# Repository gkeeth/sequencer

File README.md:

# 8-step CV sequencer

Simple 8-step, 0-5V CV sequencer for synthesizers.

* Each step has an adjustable CV (0-5V)
* Clock is internally generated, but can also be provided externally
* Internal clock has adjustable frequency and duty cycle
* CV and clock outputs

Powered from a 9V battery.

This is a KiCad v7 project.

## License
Hardware design files are licensed under a [Creative Commons Attribution-ShareAlike 4.0
International License][cc-by-sa].

[![CC BY-SA 4.0][cc-by-sa-image]][cc-by-sa]

Code is licensed under the MIT license.

[![License: MIT][mit-shield]][mit-link]

[cc-by-sa]: http://creativecommons.org/licenses/by-sa/4.0/
[cc-by-sa-image]: https://licensebuttons.net/l/by-sa/4.0/88x31.png
[cc-by-sa-shield]: https://img.shields.io/badge/License-CC%20BY--SA%204.0-lightgrey.svg
[mit-link]: https://opensource.org/licenses/MIT
[mit-shield]: https://img.shields.io/badge/License-MIT-yellow.svg

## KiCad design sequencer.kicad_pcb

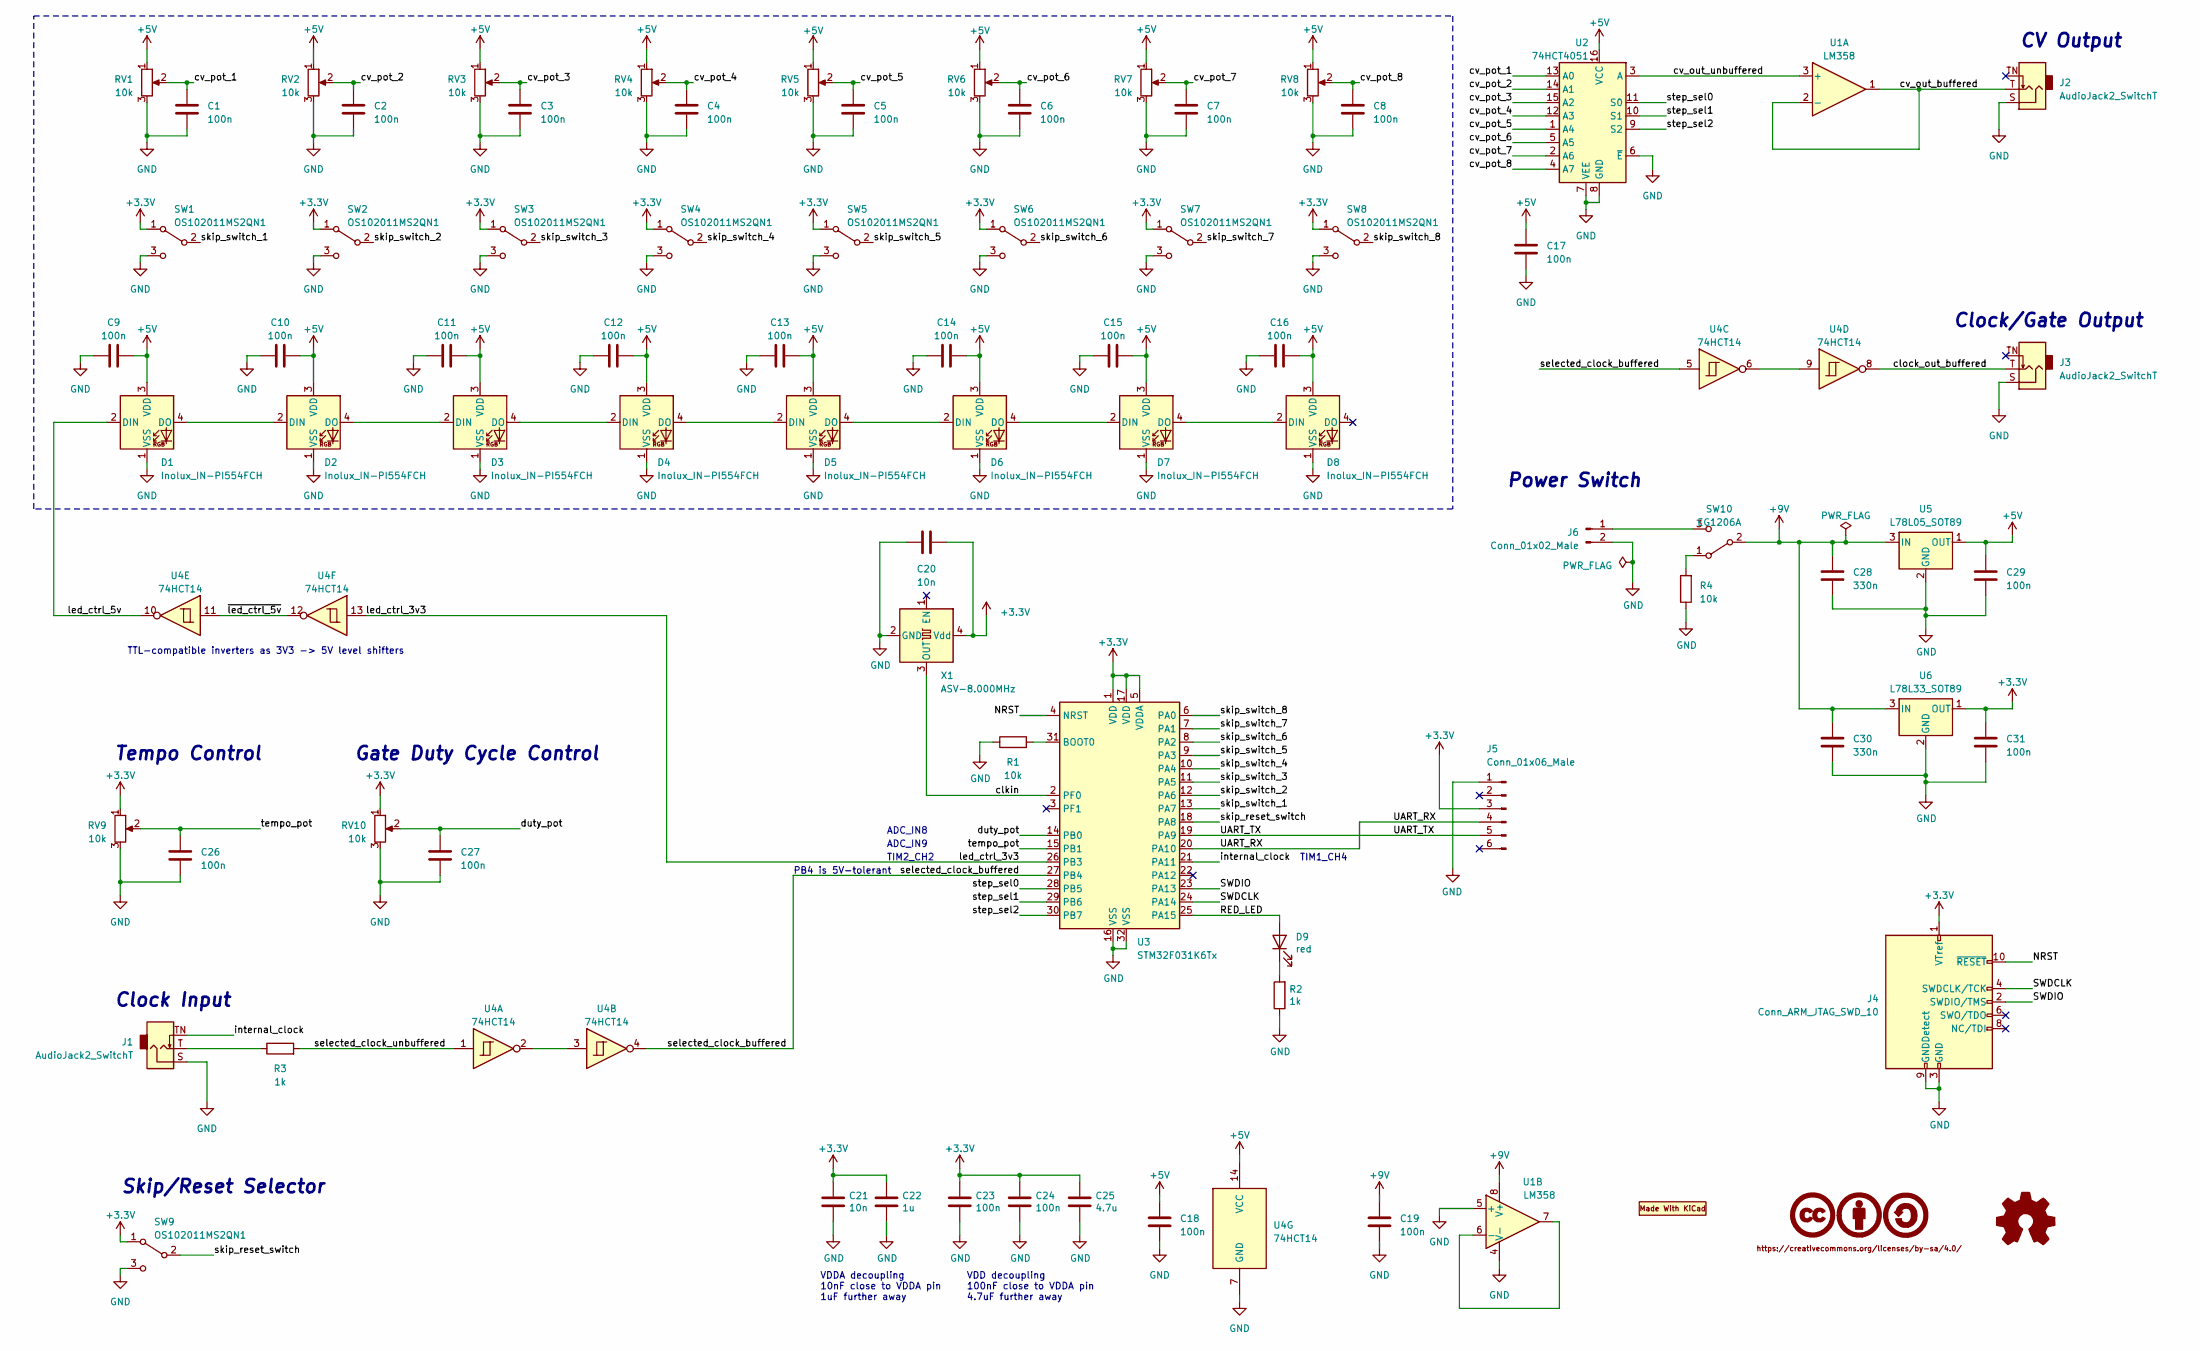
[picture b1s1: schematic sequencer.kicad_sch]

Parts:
C1, C2, C3, C4, C5, C6, C7, C8, C9, C10, C11, C12, C13, C14, C15, C16, C17, C18, C19, C23, C24, C26, C27, C29, C31: 100n; C_0603_1608Metric
C20, C21: 10n; C_0603_1608Metric
C22: 1u; C_0805_2012Metric; Manufacturer PN C0805C105K3RACTU
C25: 4.7u; C_0805_2012Metric; Manufacturer PN C0805C475K4RACTU
C28, C30: 330n; C_0805_2012Metric
D1, D2, D3, D4, D5, D6, D7, D8: Inolux_IN-PI554FCH; LED_Inolux_IN-PI554FCH_PLCC4_5.0x5.0mm_P3.2mm
D9: red; LED_0603_1608Metric; Manufacturer PN LTST-C191KRKT
J1, J2, J3: AudioJack2_SwitchT; Jack_3.5mm_QingPu_WQP-PJ398SM_Vertical_CircularHoles
J4: Conn_ARM_JTAG_SWD_10; PinHeader_2x05_P1.27mm_Vertical_SMD
J5: Conn_01x06_Male; PinHeader_1x06_P2.54mm_Horizontal
J6: Conn_01x02_Male; Molex_SL_A-70553-0001_1x02_P2.54mm_Horizontal
LOGO1: CC-BY-SA_0.33in; CC-BY-SA_SilkScreenTop_Small
LOGO2: Logo_MadeWithKiCad; KiCad-Logo2_5mm_SilkScreen
LOGO3: Logo_Open_Hardware_Small; OSHW-Logo2_7.3x6mm_SilkScreen
R1, R4: 10k; R_0603_1608Metric
R2: 1k; R_0603_1608Metric; Manufacturer PN RT0603FRE071KL
R3: 1k; R_0603_1608Metric
RV1, RV2, RV3, RV4, RV5, RV6, RV7, RV8, RV9, RV10: 10k; Potentiometer_Bourns_PTV09A-1_Single_Vertical; Manufacturer PN PTV09A-4020F-B103
SW1, SW2, SW3, SW4, SW5, SW6, SW7, SW8, SW9: OS102011MS2QN1; SW_Slide_1P2T_CK_OS102011MS2Q
SW10: EG1206A; SW_Slide_SPDT_E-Switch_EG1206A; Manufacturer PN EG1206A
U1: LM358; SOIC-8_3.9x4.9mm_P1.27mm
U2: 74HCT4051; SOIC-16_3.9x9.9mm_P1.27mm
U3: STM32F031K6Tx; LQFP-32_7x7mm_P0.8mm
U4: 74HCT14; SOIC-14_3.9x8.7mm_P1.27mm
U5: L78L05_SOT89; SOT-89-3
U6: L78L33_SOT89; SOT-89-3
X1: ASV-8.000MHz; Oscillator_SMD_Abracon_ASV-4Pin_7.0x5.1mm

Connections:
+3.3V: C20.1, C21.1, C22.1, C23.1, C24.1, C25.1, C31.2, J4.1 (VTref), J5.3, RV9.1, RV10.1, SW1.1 (A), SW2.1 (A), SW3.1 (A), SW4.1 (A), SW5.1 (A), SW6.1 (A), SW7.1 (A), SW8.1 (A), SW9.1 (A), U3.1 (VDD), U3.5 (VDDA), U3.17 (VDD), U6.1 (OUT), X1.4 (Vdd)
+5V: C9.1, C10.1, C11.1, C12.1, C13.1, C14.1, C15.1, C16.1, C17.2, C18.2, C29.2, D1.3 (VDD), D2.3 (VDD), D3.3 (VDD), D4.3 (VDD), D5.3 (VDD), D6.3 (VDD), D7.3 (VDD), D8.3 (VDD), RV1.1, RV2.1, RV3.1, RV4.1, RV5.1, RV6.1, RV7.1, RV8.1, U2.16 (VCC), U4.14 (VCC), U5.1 (OUT)
+9V: C19.2, C28.1, C30.1, SW10.2 (B), U1.8 (V+), U5.3 (IN), U6.3 (IN)
/NRST: J4.10 (~RESET), U3.4 (NRST)
/RED_LED: D9.2 (A), U3.25 (PA15)
/SWDCLK: J4.4 (SWDCLK/TCK), U3.24 (PA14)
/SWDIO: J4.2 (SWDIO/TMS), U3.23 (PA13)
/UART_RX: J5.4, U3.20 (PA10)
/UART_TX: J5.5, U3.19 (PA9)
/clkin: U3.2 (PF0), X1.3 (OUT)
/clock_out_buffered: J3.T, U4.8
/cv_out_buffered: J2.T, U1.1, U1.2 (-)
/cv_out_unbuffered: U1.3 (+), U2.3 (A)
/cv_pot_1: C1.2, RV1.2, U2.13 (A0)
/cv_pot_2: C2.2, RV2.2, U2.14 (A1)
/cv_pot_3: C3.2, RV3.2, U2.15 (A2)
/cv_pot_4: C4.2, RV4.2, U2.12 (A3)
/cv_pot_5: C5.2, RV5.2, U2.1 (A4)
/cv_pot_6: C6.2, RV6.2, U2.5 (A5)
/cv_pot_7: C7.2, RV7.2, U2.2 (A6)
/cv_pot_8: C8.2, RV8.2, U2.4 (A7)
/duty_pot: C27.2, RV10.2, U3.14 (PB0)
/internal_clock: J1.TN, U3.21 (PA11)
/led_ctrl_3v3: U3.26 (PB3), U4.13
/led_ctrl_5v: D1.2 (DIN), U4.10
/selected_clock_buffered: U3.27 (PB4), U4.4, U4.5
/selected_clock_unbuffered: R3.2, U4.1
/skip_reset_switch: SW9.2 (B), U3.18 (PA8)
/skip_switch_1: SW1.2 (B), U3.13 (PA7)
/skip_switch_2: SW2.2 (B), U3.12 (PA6)
/skip_switch_3: SW3.2 (B), U3.11 (PA5)
/skip_switch_4: SW4.2 (B), U3.10 (PA4)
/skip_switch_5: SW5.2 (B), U3.9 (PA3)
/skip_switch_6: SW6.2 (B), U3.8 (PA2)
/skip_switch_7: SW7.2 (B), U3.7 (PA1)
/skip_switch_8: SW8.2 (B), U3.6 (PA0)
/step_sel0: U2.11 (S0), U3.28 (PB5)
/step_sel1: U2.10 (S1), U3.29 (PB6)
/step_sel2: U2.9 (S2), U3.30 (PB7)
/tempo_pot: C26.2, RV9.2, U3.15 (PB1)
/~led_ctrl_5v: U4.11, U4.12
GND: C1.1, C2.1, C3.1, C4.1, C5.1, C6.1, C7.1, C8.1, C9.2, C10.2, C11.2, C12.2, C13.2, C14.2, C15.2, C16.2, C17.1, C18.1, C19.1, C20.2, C21.2, C22.2, C23.2, C24.2, C25.2, C26.1, C27.1, C28.2, C29.1, C30.2, C31.1, D1.1 (VSS), D2.1 (VSS), D3.1 (VSS), D4.1 (VSS), D5.1 (VSS), D6.1 (VSS), D7.1 (VSS), D8.1 (VSS), J1.S, J2.S, J3.S, J4.3 (GND), J4.5 (GND), J4.9 (GNDDetect), J5.1, J6.2, R1.1, R2.1, R4.1, RV1.3, RV2.3, RV3.3, RV4.3, RV5.3, RV6.3, RV7.3, RV8.3, RV9.3, RV10.3, SW1.3 (C), SW2.3 (C), SW3.3 (C), SW4.3 (C), SW5.3 (C), SW6.3 (C), SW7.3 (C), SW8.3 (C), SW9.3 (C), U1.4 (V-), U1.5 (+), U2.6 (~E), U2.7 (VEE), U2.8 (GND), U3.16 (VSS), U3.32 (VSS), U4.7 (GND), U5.2 (GND), U6.2 (GND), X1.2 (GND)
unnamed: D1.4 (DO), D2.2 (DIN)
unnamed: D2.4 (DO), D3.2 (DIN)
unnamed: D3.4 (DO), D4.2 (DIN)
unnamed: D4.4 (DO), D5.2 (DIN)
unnamed: D5.4 (DO), D6.2 (DIN)
unnamed: D6.4 (DO), D7.2 (DIN)
unnamed: D7.4 (DO), D8.2 (DIN)
unnamed: D9.1 (K), R2.2
unnamed: J1.T, R3.1
unnamed: J6.1, SW10.3 (C)
unnamed: R4.2, SW10.1 (A)
unnamed: U1.6 (-), U1.7
unnamed: R1.2, U3.31 (BOOT0)
unnamed: U4.2, U4.3
unnamed: U4.6, U4.9

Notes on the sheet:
ADC_IN9
CV Output
Gate Duty Cycle Control
Tempo Control
Clock Input
VDDA decoupling 10nF close to VDDA pin 1uF further away
TIM1_CH4
Skip/Reset Selector
VDD decoupling 100nF close to VDDA pin 4.7uF further away
Clock/Gate Output
ADC_IN8
TIM2_CH2
TTL-compatible inverters as 3V3 -> 5V level shifters
PB4 is 5V-tolerant
Power Switch

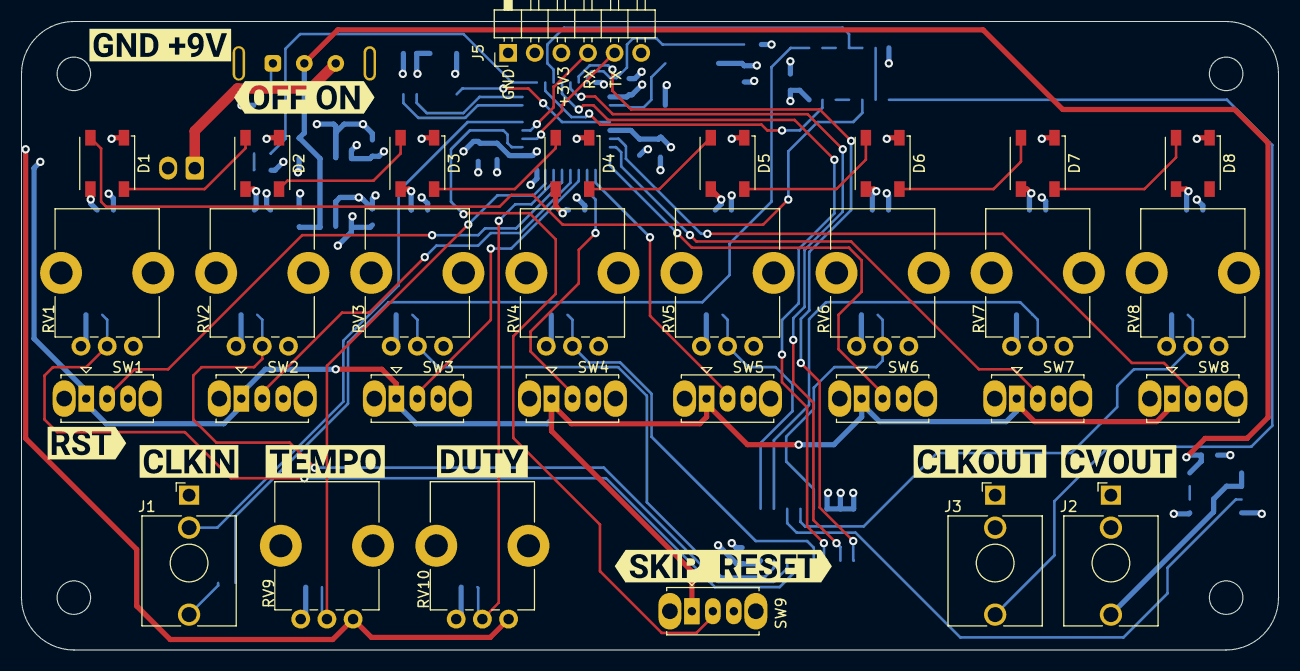
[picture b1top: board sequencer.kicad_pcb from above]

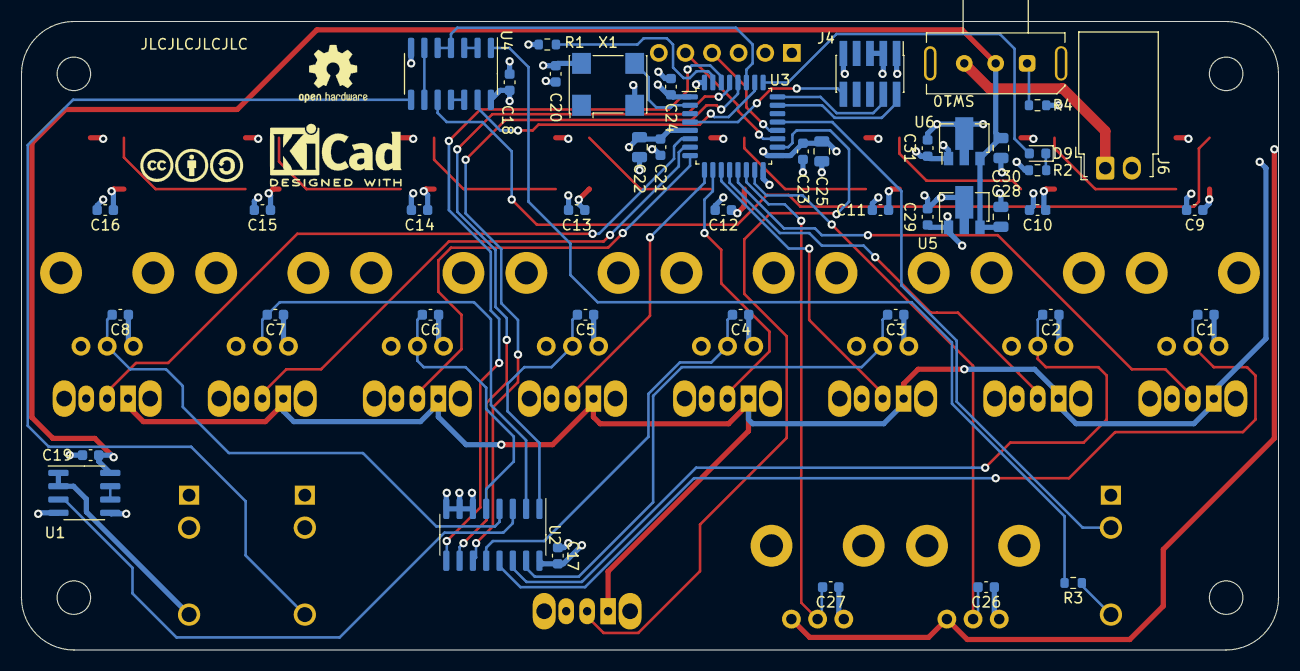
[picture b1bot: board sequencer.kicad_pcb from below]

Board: 4 copper layers, 120.0 x 60.0 mm, 89 parts (49 on the bottom side), 57 nets.

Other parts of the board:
kibuzzard-63F425C8: G***; kibuzzard-63F425C8
kibuzzard-63F425D0: G***; kibuzzard-63F425D0
kibuzzard-63F427E2: G***; kibuzzard-63F427E2
kibuzzard-63F428B8: G***; kibuzzard-63F428B8
kibuzzard-63F428D5: G***; kibuzzard-63F428D5
kibuzzard-63F42616: G***; kibuzzard-63F42616
kibuzzard-63F42620: G***; kibuzzard-63F42620
kibuzzard-63F42641: G***; kibuzzard-63F42641
kibuzzard-63F42779: G***; kibuzzard-63F42779

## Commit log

2022-12-18 Complete TODOs
    - assign all footprints except pots
    - hook up duty cycle pot
    - add power switch
    - switch to HCT inverters for logic level compatibility with 3.3V CMOS
2022-12-18 add footprints to pots
2022-12-18 mostly complete placement
2022-12-19 initial routing complete, DRC errors clean
2022-12-19 DRC clean, moved refdeses
2022-12-19 Circuit fixes and cleanup
    - minor schematic rearranging
    - checking I/O levels between MCU and 5V logic (still need to check
    switch selection bits)
    - change switches to 3V3, re-route
2022-12-28 clarify kicad v7
2023-01-14 change analog switch to HCT
2023-02-21 add labels
2023-02-21 update pot footprints from library
2023-02-21 r0 fab
2023-03-11 add TODO list for next hw rev
2023-03-11 ignore binaries
2023-03-11 ignore fab and xml files
2023-03-11 add basic code (just blink and uart)
2023-03-12 Update makefile
    - define OOCD_FILE so `make flash` works
    - rearrange includes so that `make debug` isn't the default target (TBD
    if this is good or not)
2023-03-12 add ADC functionality for reading tempo and duty pots
2023-03-12 remove sequencer/blink from gitignore because they ignore the folders
2023-03-14 roughly working unit test framework
2023-03-14 ignore test executable
2023-03-17 add basic tempo/duty impl with tests
2023-03-22 add min/max util functions
2023-03-22 add assert to utils
2023-03-22 uart with tests
2023-03-23 reduce number of min/max functions
2023-03-23 add uart send string/line functions
2023-03-23 add uart printing to assert
2023-03-23 move uart setup out of main file
2023-03-23 move clock setup/systick out of main file
2023-03-24 abstract uart echoing out into the uart driver
2023-03-25 move ADC reads, average updates into pot driver
2023-03-26 make adc trigger off of tim3
2023-03-28 add debounced switch driver
2023-03-29 move board led control into its own driver
2023-04-02 clean up flags and includes in makefile
2023-04-02 add language server file generation to makefile
2023-04-05 Rough PWM working
2023-04-05 Remove some PWM debug code
2023-04-05 Make PWM code more generic for 2 peripherals
2023-04-06 map duty pot onto clock duty cycle
2023-04-07 Rename map to map_range
2023-04-09 WIP tempo/duty control of clock without overflowing
2023-04-09 Rename test stubs to match real functions
2023-04-14 Add tests for ASSERT, and some other plumbing
2023-04-14 Complete timer_ms_to_arr tests, with assertions
2023-04-14 Add code license
2023-04-14 Rename assert test variables/functions
2023-04-14 Clean up comments
2023-04-14 Split assert tests into their own file
2023-04-14 Add missing check to assert tests
2023-04-14 Rename assert fake
2023-04-16 complete unit tests and cleanup for ms_to_arr
2023-04-16 Simplify assert fake
2023-04-16 Refactor ms_to_arr assertion tests
2023-04-16 Fix target build
2023-04-16 Clean up asserts and comments
2023-04-17 Add some python scripts for analyzing error
2023-04-18 Add better API for setting sequencer tempo
    mostly untested, but it builds. Also needs to be cleaned up.
2023-04-19 minor makefile updates
2023-04-19 API description TODO comment
2023-04-19 some makefile/bear changes
2023-04-19 Fix assert typo
2023-04-19 Fix typo in calculating duty
2023-04-19 Add tests for duty_to_pwm_compare()
    - fix existing tests for function signature changes
    - fix a bug in duty_to_pwm_compare() allowing div-by-zero and remove now
    unnecessary code
2023-04-19 Clean up main loop, remove some debug code
2023-04-20 Improve assert fake slightly
2023-04-20 Add tests for tempo_to_period_and_prescaler()
2023-04-20 Add description comment for duty_to_pwm_compare()
2023-04-21 Move most platform.c funcs into platform_<func>.c
2023-04-21 Switch language server tooling to .ccls
    compile_commands.json needed to be regenerated for every new file, and
    bear doesn't work super well on mac with non-standard compilers (e.g.
    arm-none-eabi-gcc)
2023-04-21 add Wconversion warning
2023-04-22 Add unit tests and asserts for timer_hz_to_arr()
2023-04-22 Implement + test timer_ns_to_arr()
2023-04-22 Avoid some implicit conversions
2023-04-22 Add warning flags to test build as well
2023-04-22 Fix a lot of warnings
2023-04-22 Remove dead code
2023-04-22 Add an additional assert in timer_ns_to_arr()
2023-04-22 add a make all target
2023-04-22 More warning fixes
2023-04-28 Gross code to get LED DMA working
2023-04-28 Make GDB less annoying
2023-04-28 Add a bit_set utility function
2023-04-28 Working LED PWM prototype
    ADC temporarily disabled because it interferes with the LED PWM and
    locks the part...
2023-04-30 Refactor pot reading/averaging
    (prep for using a ping pong DMA'd buffer for pot readings)
2023-05-02 More work for ADC DMA
2023-05-02 Get ADC DMA working (but it breaks LED DMA)
2023-05-02 temporarily fix LEDs
2023-05-03 Some cleanup of PWM/LED setup
2023-05-03 Rename clocks.c to system_clocks.h
    It was confusing with the sequencer clock
2023-05-04 Refactoring
    - pwm.{c,h} didn't have anything meaningful in it, merged with
    tempo_and_duty.{c,h}
    - renamed some functions to be more clear
    - moved some function comments from c files to h files
    - improved some function comments
2023-05-04 Move more comments from c files to headers
2023-05-05 Use openocd via pipe instead of TCP
    also define a reload command, and ignore the openocd log
2023-05-05 Enable all 8 step LEDs
    for now they just toggle through christmas tree colors.
    Also make the LEDs less blindingly bright
2023-05-13 Reorganize switch debouncing constants
2023-05-13 Add tests for step_leds
2023-05-13 step_leds: add led_set_for_step() and tests
    doesn't yet handle disabled/skipped steps
2023-05-13 add comments for ideal PWM compare values
2023-05-13 Rename step_leds to steps
2023-05-19 Implement basic LED step toggling
    - hardcoded tempo and switches
    - BUG: when first LED resets, the remaining LEDs don't light up
2023-05-19 Add a is_step_skipped() helper
2023-05-19 Fix LED bug when first step was disabled
    Also rename some LED functions
2023-05-20 Implement reading/debouncing switches
2023-05-25 Make appropriate step leds come up on reset
    - don't hardcode initial leds to all red
    - note: switches aren't debounced for 16ms so initial state of disabled
    switches is incorrect until the first step after a full debounce
    cycle. This could be fixed by delaying for 16ms before turning on the
    lights (16ms is probably not noticeable), by preloading the debounced
    switch state (not ideal), or by changing the debounce algorithm.
2023-05-25 Factor read switches/set led buffer into a helper
2023-05-25 Make many step LED functions static
    - move LED buffer into platform_pwm.c and out of steps.c as it is a DMA
    buffer
    - make step LED functions that don't get called by outside customers
    static
    - unit tests currently broken, as static functions are not testable
    directly
2023-05-26 Implement analog CV mux control
2023-07-11 build fixes
2023-07-11 rename confusing switch function
2023-07-11 Use rising edge of clkin to advance sequencer
2023-07-16 Abstract pot value mapping into helper functions
2023-07-16 cleanup TODO in umap_range
2023-07-16 Fixup initial setup to not use hardcoded values
2023-07-16 Clean up some TODOs
2023-07-22 Add analysis script for checking tempo error
2023-08-05 WIP, not working refactor. Builds but LEDs don't work.
2023-08-08 Fix LEDs in refactor
    DMA channel needs to be disabled when it's set up. The refactored
    code would trigger the dma (enable the channel) every time the timer
    interrupt fired, which started prior to DMA setup.
2023-08-08 Merge platform_pwm.c into platform.c
    There's a lot of coupling with shared buffers and overlap in
    functionality. It simplifies things to combine them even if the
    resulting file is quite long.
2023-08-08 Refactor tick timer interrupt
    also clean some TODOs and improve documentation
2023-08-08 Remove unused functions and clean more TODOs

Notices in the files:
sequencer.kicad_sch:
https://creativecommons.org/licenses/by-sa/4.0
